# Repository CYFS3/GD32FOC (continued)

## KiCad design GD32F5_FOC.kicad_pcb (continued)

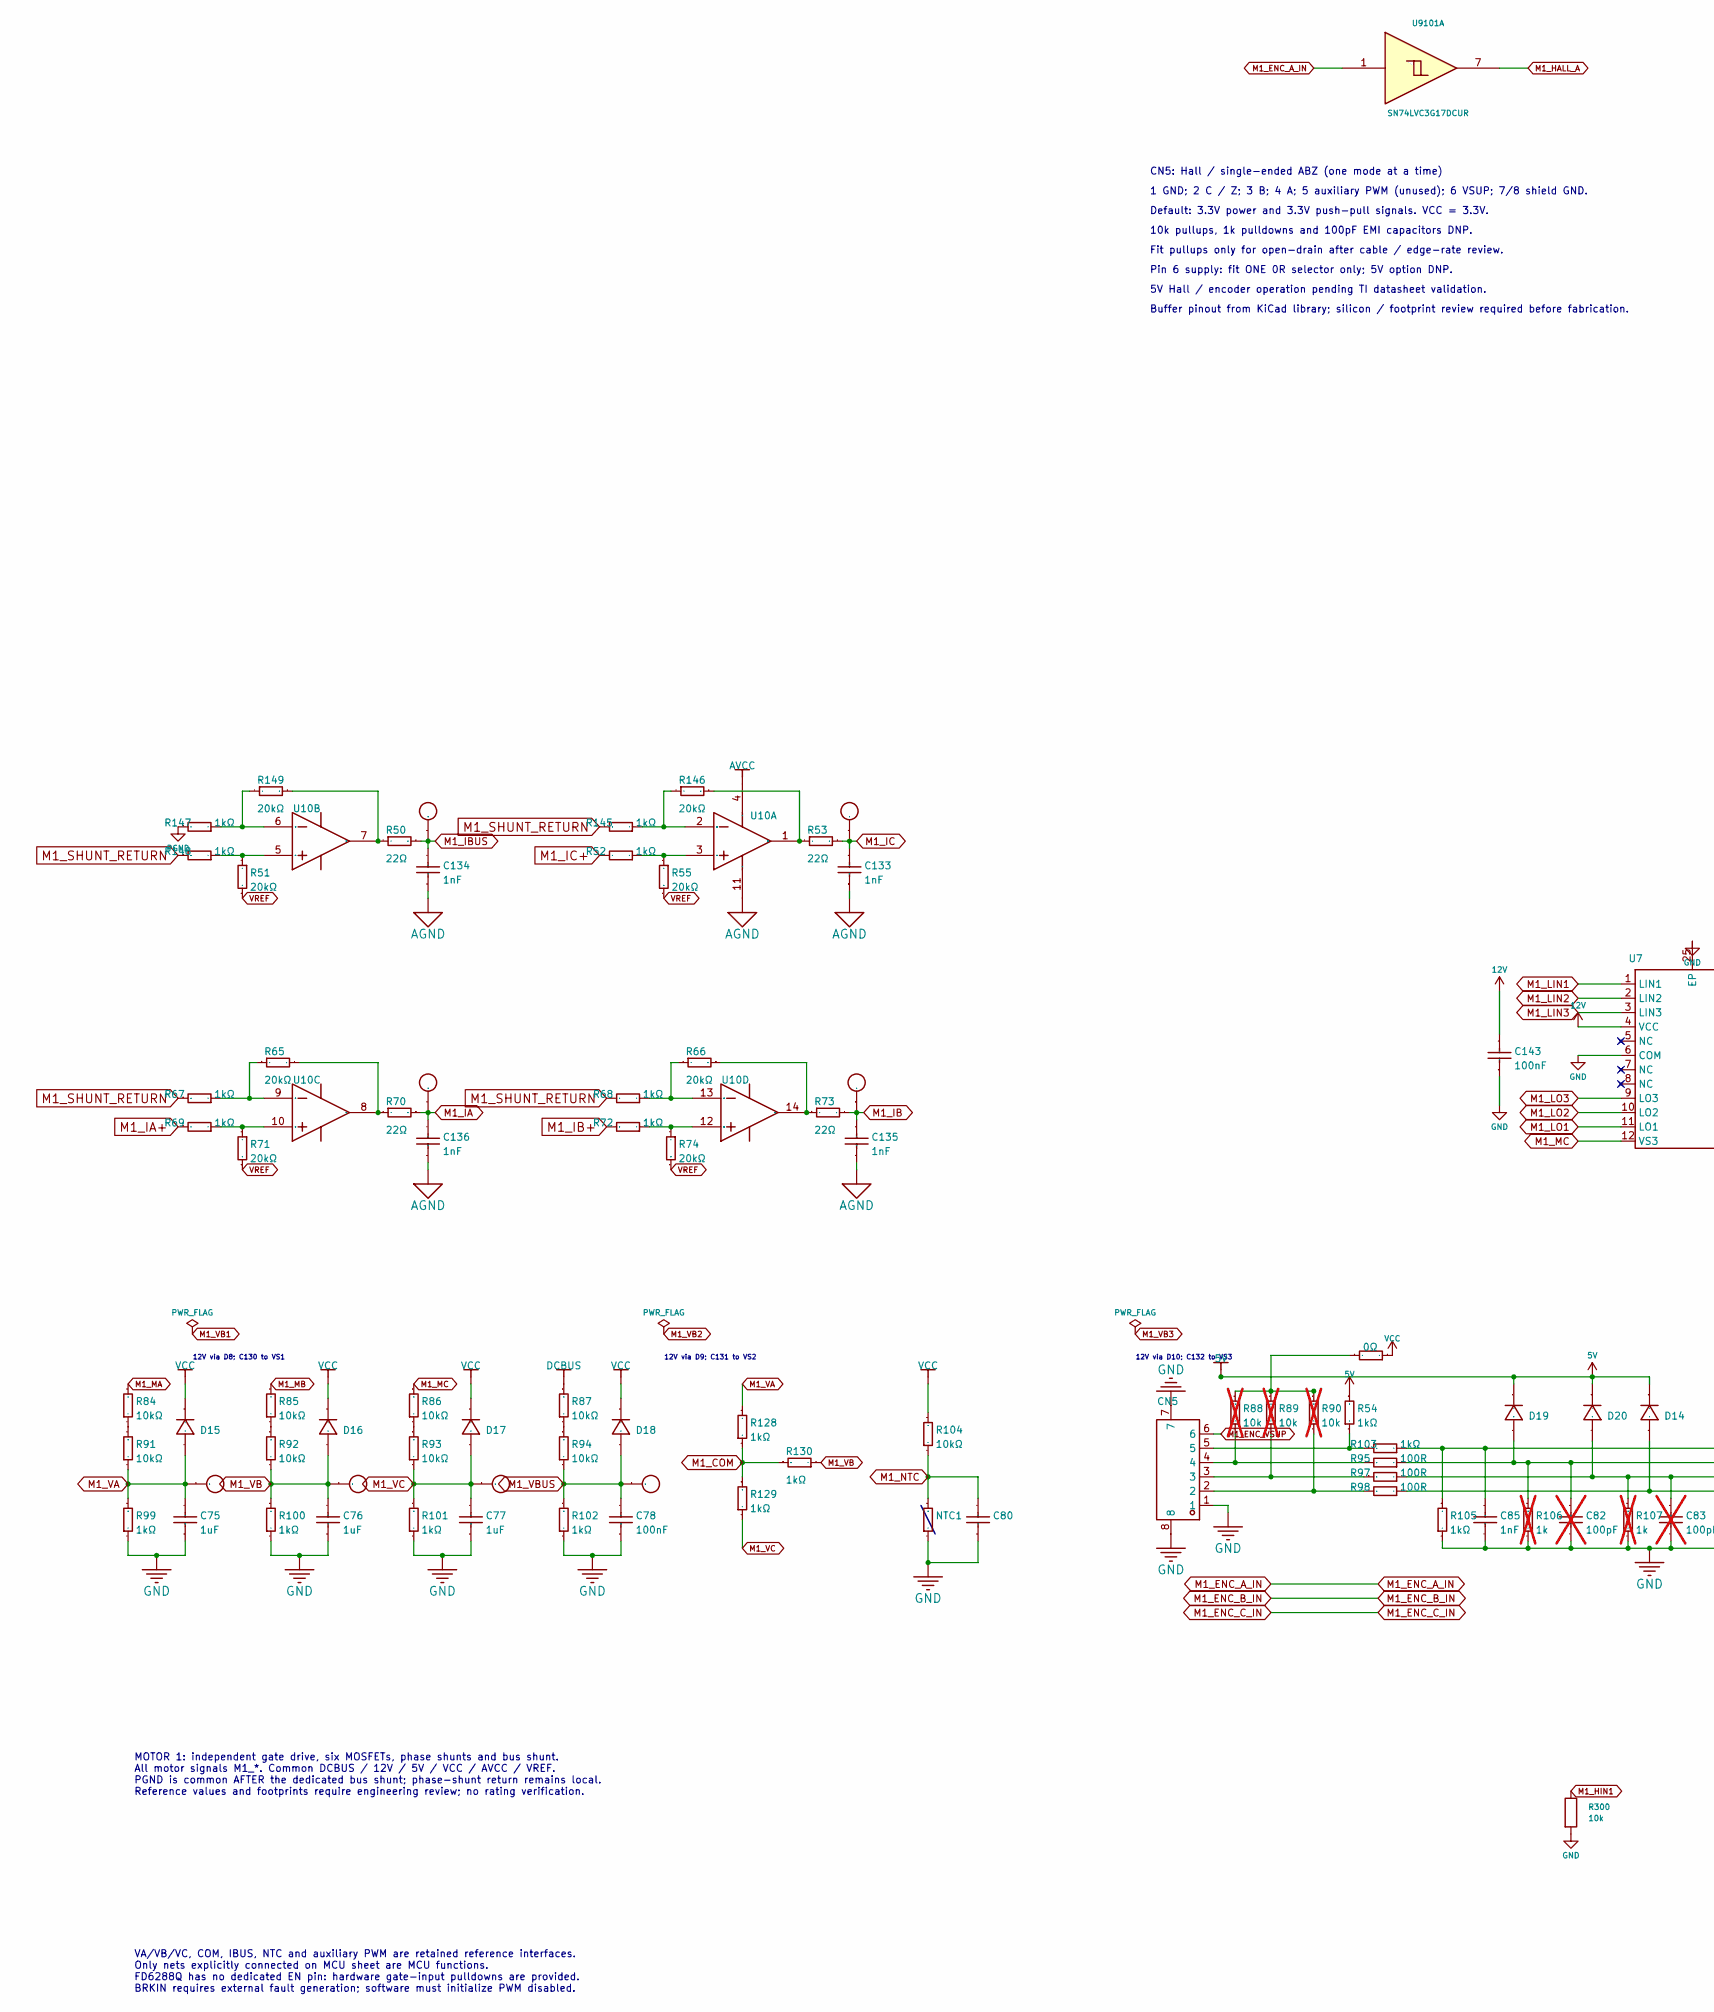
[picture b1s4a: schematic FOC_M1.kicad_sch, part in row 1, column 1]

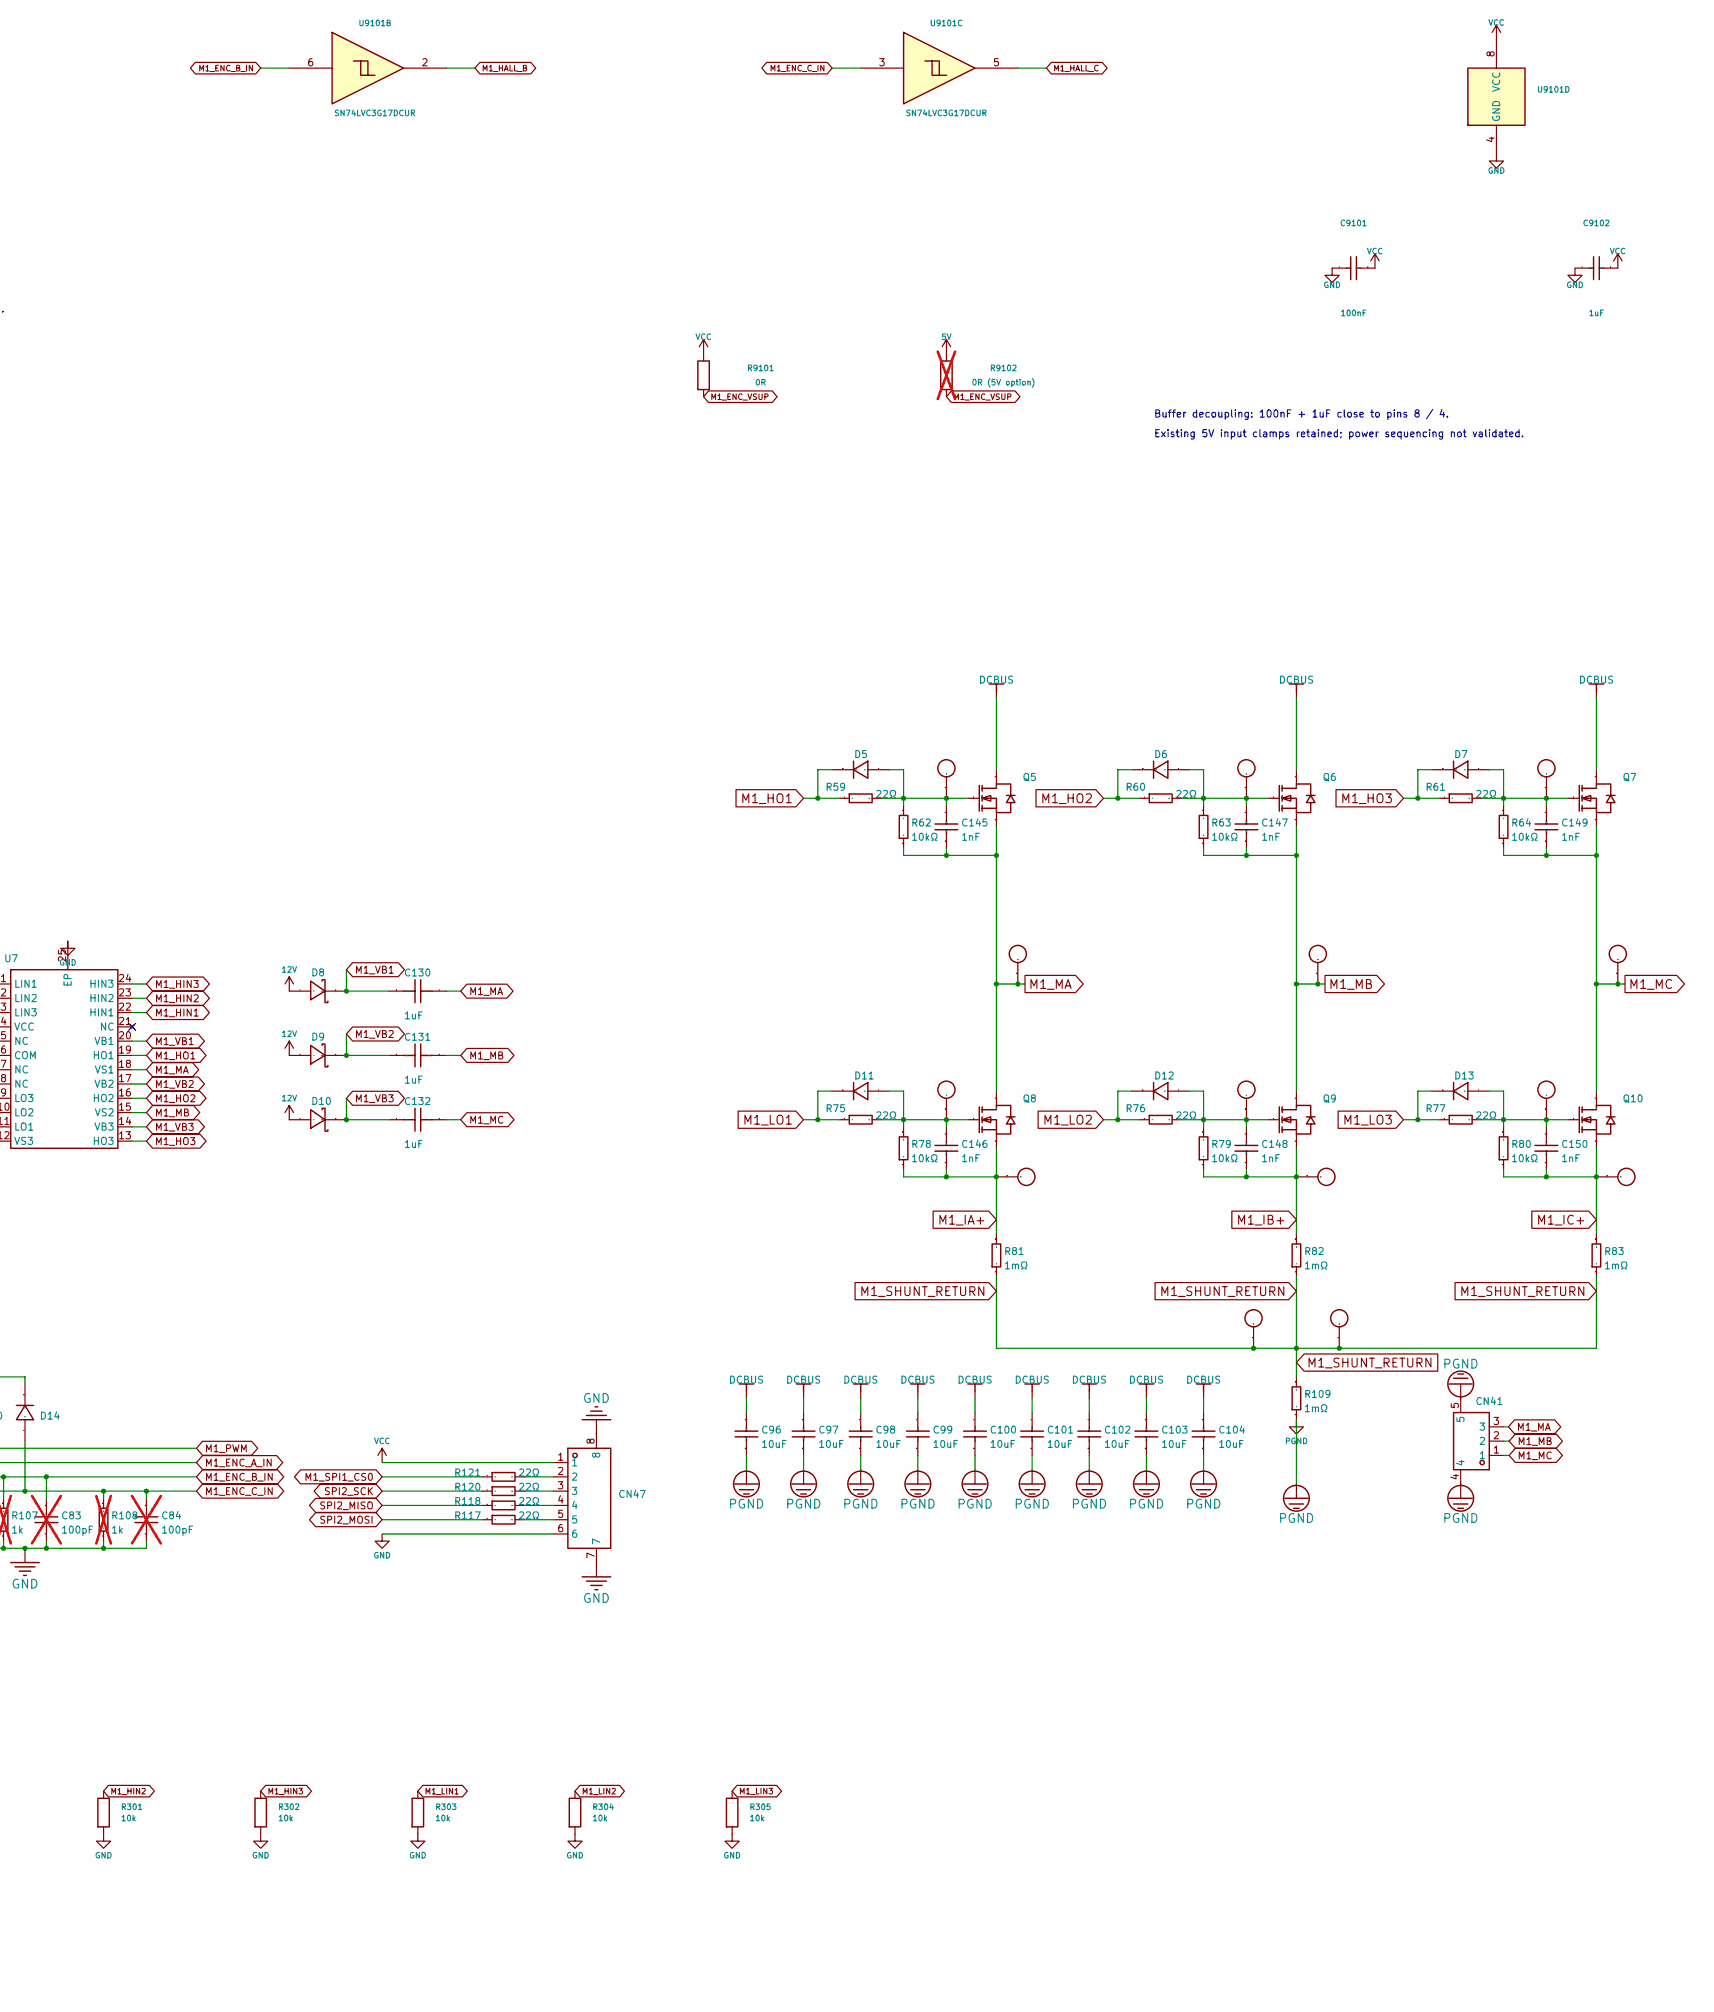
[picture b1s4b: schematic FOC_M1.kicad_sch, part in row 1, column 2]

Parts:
C75, C76, C77: 1uF; C0603_S; Tolerance ±10%; Voltage Rated 50V; Manufacturer Part 0603B102K500NT; LCSC Part Name 1nF ±10% 50V
C78, C80: 100nF; C0603_S; Tolerance ±10%; Voltage Rated 50V; Manufacturer Part 0603B102K500NT; LCSC Part Name 1nF ±10% 50V
C82, C83, C84: 100pF; C0603_S; not fitted
C85: 1nF; C0603_S; Tolerance ±10%; Voltage Rated 50V; Manufacturer Part 0603B104K500NT; LCSC Part Name 100nF ±10% 50V
C96, C97, C98, C99, C100, C101, C102, C103, C104: 10uF; C_1206_3216Metric; Tolerance ±10%; Voltage Rated 50V; Manufacturer Part CL31A106KBHNNNE; LCSC Part Name 10uF ±10% 50V
C130, C131, C132: 1uF; C0603; Tolerance ±10%; Voltage Rating 50V; Manufacturer Part CGA0603X5R105K500JT; LCSC Part Name 1uF ±10% 50V
C133, C134, C135, C136, C145, C146, C147, C148, C149, C150: 1nF; C0603_S; Tolerance ±10%; Voltage Rated 50V; Manufacturer Part 0603B102K500NT; LCSC Part Name 1nF ±10% 50V
C143: 100nF; C0603_S; Tolerance ±10%; Voltage Rated 50V; Manufacturer Part 0603B104K500NT; LCSC Part Name 100nF ±10% 50V
C9101: 100nF; C0603_S
C9102: 1uF; C0603_S
CN5, CN47: WAFER-GH1.25-6PWB; CONN-SMD_6P-P1.25_XUNPU_WAFER-GH1.25-6PWB; Current Rating (Max) 1A; Manufacturer Part WAFER-GH1.25-6PWB; LCSC Part Name GH1.25mm6P卧贴带扣带扣
CN14, CN15, CN17, CN18, CN19, CN20, CN21, CN22, CN23, CN24, CN25, CN26, CN27, CN28, CN29, CN30, CN35, CN36, CN37, CN38, CN39, CN40: TestPoint; TestPoint_D1.27_Reference; LCSC Part Name 测试点
CN41: MR30PW-F; CONN-TH_MR30PW-F; Manufacturer Part MR30PW-F; LCSC Part Name MR30PW-F
D5, D6, D7, D11, D12, D13, D14, D15, D16, D17, D18, D19, D20: B16WS; SOD-323_L1.8-W1.3-LS2.5-RD_2; Forward Voltage (Vf@If) 700mV@1A; Reverse Voltage (Vr) 60V; Manufacturer Part B16WS; LCSC Part Name B16WS
D8, D9, D10: B16WS; D_SOD-323; Forward Voltage (Vf@If) 650mV@1A; Manufacturer Part B16WS; LCSC Part Name B16WS
NTC1: NCP18XH103F03RB; R0603_S; Resistance Tolerance ±1%; Manufacturer Part NCP18XH103F03RB; LCSC Part Name 10kΩ 电阻精度:±1% 3380K
Q5, Q6, Q7, Q8, Q9, Q10: NCE7560K; Manufacturer Part NCE7560K; LCSC Part Name N沟道 75V 60A
R49: 0Ω; R0603_S; Overload Voltage (Max) 50V; Tolerance ±1%; Manufacturer Part RS-03000FT; LCSC Part Name 0Ω ±1% 100mW
R50, R53, R59, R60, R61, R70, R73, R75, R76, R77, R117, R118, R120, R121: 22Ω; R0603_S; Overload Voltage (Max) 75V; Tolerance ±1%; Manufacturer Part 0603WAF220JT5E; LCSC Part Name 22Ω ±1% 100mW 厚膜电阻
R51, R55, R65, R66, R71, R74, R146, R149: 20kΩ; R0603_S; Overload Voltage (Max) 75V; Tolerance ±0.1%; Manufacturer Part RT0603BRD0720KL; LCSC Part Name 20kΩ ±0.1% 100mW
R52, R67, R68, R69, R72, R145, R147, R148: 1kΩ; R0603_S; Overload Voltage (Max) 75V; Tolerance ±0.1%; Manufacturer Part RT0603BRD071KL; LCSC Part Name 1kΩ ±0.1% 100mW
R54, R103, R105, R128, R129, R130: 1kΩ; R0603_S; Overload Voltage (Max) 75V; Tolerance ±1%; Manufacturer Part 0603WAF1002T5E; LCSC Part Name 10kΩ ±1% 100mW 厚膜电阻
R62, R63, R64, R78, R79, R80, R104: 10kΩ; R0603_S; Overload Voltage (Max) 75V; Tolerance ±1%; Manufacturer Part 0603WAF1002T5E; LCSC Part Name 10kΩ ±1% 100mW 厚膜电阻
R81, R82, R83, R109: 1mΩ; R_2512_6332Metric
R84, R85, R86, R87, R91, R92, R93, R94: 10kΩ; R0603_S; Overload Voltage (Max) 75V; Tolerance ±1%; Manufacturer Part 0603WAF1502T5E; LCSC Part Name 15kΩ ±1% 100mW 厚膜电阻
R88, R89, R90: 10k; R0603_S; not fitted
R95, R97, R98: 100R; R0603_S
R99, R100, R101, R102: 1kΩ; R0603_S; Overload Voltage (Max) 75V; Tolerance ±1%; Manufacturer Part 0603WAF2001T5E; LCSC Part Name 2kΩ ±1% 100mW 厚膜电阻
R106, R107, R108: 1k; R0603_S; not fitted
R300, R301, R302, R303, R304, R305: 10k; R_0603_1608Metric
R9101: 0R; R_0603_1608Metric
R9102: 0R (5V option); R_0603_1608Metric; not fitted
U7: FD6288Q; QFN-24_L4.0-W4.0-P0.50-BL-EP2.6; Manufacturer Part FD6288Q; LCSC Part Name FD6288Q
U10: RS624XQ; TSSOP-14_4.4x5mm_P0.65mm; Manufacturer Part RS624XQ; LCSC Part Name 低噪声运放RS624XQ
U9101: SN74LVC3G17DCUR; VSSOP-8_2.3x2mm_P0.5mm

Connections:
5V: D14.1 (-), D19.1 (-), D20.1 (-), R54.1, R9102.1; also elsewhere on the board
12V: C143.2, D8.2, D9.2, D10.2, U7.4 (VCC); also elsewhere on the board
AGND: C133.1, C134.1, C135.1, C136.1, U10.11 (V-); also elsewhere on the board
AVCC: U10.4 (V+); also elsewhere on the board
DCBUS: C96.2, C97.2, C98.2, C99.2, C100.2, C101.2, C102.2, C103.2, C104.2, Q5.2 (D), Q6.2 (D), Q7.2 (D), R87.1; also elsewhere on the board
GND: C75.1, C76.1, C77.1, C78.1, C80.1, C82.2, C83.2, C84.2, C85.2, C143.1, C9101.2, C9102.2, CN5.1, CN5.7, CN5.8, CN47.6, CN47.7, CN47.8, NTC1.2, R99.2, R100.2, R101.2, R102.2, R105.2, R106.2, R107.2, R108.2, R300.2, R301.2, R302.2, R303.2, R304.2, R305.2, U7.6 (COM), U7.25 (EP), U9101.4 (GND); also elsewhere on the board
M1_COM: R128.2, R129.1, R130.1
M1_ENC_A_IN: C82.1, D19.2 (+), R95.2, R106.1, U9101.1
M1_ENC_B_IN: C83.1, D20.2 (+), R97.2, R107.1, U9101.6
M1_ENC_C_IN: C84.1, D14.2 (+), R98.2, R108.1, U9101.3
M1_ENC_VSUP: CN5.6, R9101.2, R9102.2
M1_HALL_A: U9101.7; also elsewhere on the board
M1_HALL_B: U9101.2; also elsewhere on the board
M1_HALL_C: U9101.5; also elsewhere on the board
M1_HIN1: R300.1, U7.22 (HIN1); also elsewhere on the board
M1_HIN2: R301.1, U7.23 (HIN2); also elsewhere on the board
M1_HIN3: R302.1, U7.24 (HIN3); also elsewhere on the board
M1_HO1: D5.1 (-), R59.2, U7.19 (HO1)
M1_HO2: D6.1 (-), R60.2, U7.16 (HO2)
M1_HO3: D7.1 (-), R61.2, U7.13 (HO3)
M1_IA: C136.2, CN20.1 (1_1), R70.1; also elsewhere on the board
M1_IA+: C146.1, CN28.1 (1_1), Q8.3 (S), R69.1, R78.2, R81.1
M1_IB: C135.2, CN21.1 (1_1), R73.1; also elsewhere on the board
M1_IB+: C148.1, CN29.1 (1_1), Q9.3 (S), R72.1, R79.2, R82.1
M1_IBUS: C134.2, CN14.1 (1_1), R50.1; also elsewhere on the board
M1_IC: C133.2, CN15.1 (1_1), R53.1; also elsewhere on the board
M1_IC+: C150.1, CN30.1 (1_1), Q10.3 (S), R52.1, R80.2, R83.1
M1_LIN1: R303.1, U7.1 (LIN1); also elsewhere on the board
M1_LIN2: R304.1, U7.2 (LIN2); also elsewhere on the board
M1_LIN3: R305.1, U7.3 (LIN3); also elsewhere on the board
M1_LO1: D11.1 (-), R75.2, U7.11 (LO1)
M1_LO2: D12.1 (-), R76.2, U7.10 (LO2)
M1_LO3: D13.1 (-), R77.2, U7.9 (LO3)
M1_MA: C130.2, C145.1, CN22.1 (1_1), CN41.3, Q5.3 (S), Q8.2 (D), R62.2, R84.1, U7.18 (VS1)
M1_MB: C131.2, C147.1, CN23.1 (1_1), CN41.2, Q6.3 (S), Q9.2 (D), R63.2, R85.1, U7.15 (VS2)
M1_MC: C132.2, C149.1, CN24.1 (1_1), CN41.1, Q7.3 (S), Q10.2 (D), R64.2, R86.1, U7.12 (VS3)
M1_NTC: C80.2, NTC1.1, R104.2; also elsewhere on the board
M1_PWM: C85.1, R103.2, R105.1
M1_SHUNT_RETURN: CN35.1 (1_1), CN36.1 (1_1), R67.1, R68.1, R81.2, R82.2, R83.2, R109.1, R145.1, R148.1
M1_SPI1_CS0: R121.2; also elsewhere on the board
M1_VA: C75.2, CN37.1 (1_1), D15.2 (+), R91.2, R99.1, R128.1
M1_VB: C76.2, CN38.1 (1_1), D16.2 (+), R92.2, R100.1, R130.2
M1_VB1: C130.1, D8.1, U7.20 (VB1)
M1_VB2: C131.1, D9.1, U7.17 (VB2)
M1_VB3: C132.1, D10.1, U7.14 (VB3)
M1_VBUS: C78.2, CN40.1 (1_1), D18.2 (+), R94.2, R102.1; also elsewhere on the board
M1_VC: C77.2, CN39.1 (1_1), D17.2 (+), R93.2, R101.1, R129.2
unnamed: CN5.2, R90.2, R98.1
unnamed: CN5.3, R89.2, R97.1
unnamed: CN5.4, R88.2, R95.1
unnamed: CN5.5, R54.2, R103.1
unnamed: CN47.2, R121.1
unnamed: CN47.3, R120.1
unnamed: CN47.4, R118.1
unnamed: CN47.5, R117.1
unnamed: C145.2, CN17.1 (1_1), D5.2 (+), Q5.1 (G), R59.1, R62.1
unnamed: C147.2, CN18.1 (1_1), D6.2 (+), Q6.1 (G), R60.1, R63.1
unnamed: C149.2, CN19.1 (1_1), D7.2 (+), Q7.1 (G), R61.1, R64.1
unnamed: C146.2, CN25.1 (1_1), D11.2 (+), Q8.1 (G), R75.1, R78.1
unnamed: C148.2, CN26.1 (1_1), D12.2 (+), Q9.1 (G), R76.1, R79.1
unnamed: C150.2, CN27.1 (1_1), D13.2 (+), Q10.1 (G), R77.1, R80.1
unnamed: R49.1, R88.1, R89.1, R90.1
unnamed: R84.2, R91.1
unnamed: R85.2, R92.1
unnamed: R86.2, R93.1
unnamed: R87.2, R94.1
unnamed: R52.2, R55.2, U10.3 (+INA)
unnamed: R145.2, R146.2, U10.2 (-INA)
unnamed: R53.2, R146.1, U10.1 (OUTA)
unnamed: R51.2, R148.2, U10.5 (+INB)
unnamed: R147.2, R149.2, U10.6 (-INB)
unnamed: R50.2, R149.1, U10.7 (OUTB)
unnamed: R69.2, R71.2, U10.10 (+INC)
unnamed: R65.2, R67.2, U10.9 (-INC)
unnamed: R65.1, R70.2, U10.8 (OUTC)
unnamed: R72.2, R74.2, U10.12 (+IND)
unnamed: R66.2, R68.2, U10.13 (-IND)
unnamed: R66.1, R73.2, U10.14 (OUTD)
PGND: C96.1, C97.1, C98.1, C99.1, C100.1, C101.1, C102.1, C103.1, C104.1, CN41.4, CN41.5, R109.2, R147.1; also elsewhere on the board
SPI2_MISO: R118.2; also elsewhere on the board
SPI2_MOSI: R117.2; also elsewhere on the board
SPI2_SCK: R120.2; also elsewhere on the board
VCC: C9101.1, C9102.1, CN47.1, D15.1 (-), D16.1 (-), D17.1 (-), D18.1 (-), R49.2, R104.1, R9101.1, U9101.8 (VCC); also elsewhere on the board
VREF: R51.1, R55.1, R71.1, R74.1; also elsewhere on the board

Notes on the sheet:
MOTOR 1: independent gate drive, six MOSFETs, phase shunts and bus shunt. All motor signals M1_*. Common DCBUS / 12V / 5V / VCC / AVCC / VREF. PGND is common AFTER the dedicated bus shunt; phase-shunt return remains local. Reference values and footprints require engineering review; no rating verifi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
VA/VB/VC, COM, IBUS, NTC and auxiliary PWM are retained reference interfaces. Only nets explicitly connected on MCU sheet are MCU functions. FD6288Q has no dedicated EN pin: hardware gate-input pulldowns are provided. BRKIN requires external fault generation; software must initialize PWM disabled.
CN5: Hall / single-ended ABZ (one mode at a time)
1 GND; 2 C / Z; 3 B; 4 A; 5 auxiliary PWM (unused); 6 VSUP; 7/8 shield GND.
Default: 3.3V power and 3.3V push-pull signals. VCC = 3.3V.
10k pullups, 1k pulldowns and 100pF EMI capacitors DNP.
Fit pullups only for open-drain after cable / edge-rate review.
Pin 6 supply: fit ONE 0R selector only; 5V option DNP.
5V Hall / encoder operation pending TI datasheet validation.
Buffer pinout from KiCad library; silicon / footprint review required before fabrication.
Buffer decoupling: 100nF + 1uF close to pins 8 / 4.
Existing 5V input clamps retained; power sequencing not validated.
12V via D8; C130 to VS1
12V via D9; C131 to VS2
12V via D10; C132 to VS3
